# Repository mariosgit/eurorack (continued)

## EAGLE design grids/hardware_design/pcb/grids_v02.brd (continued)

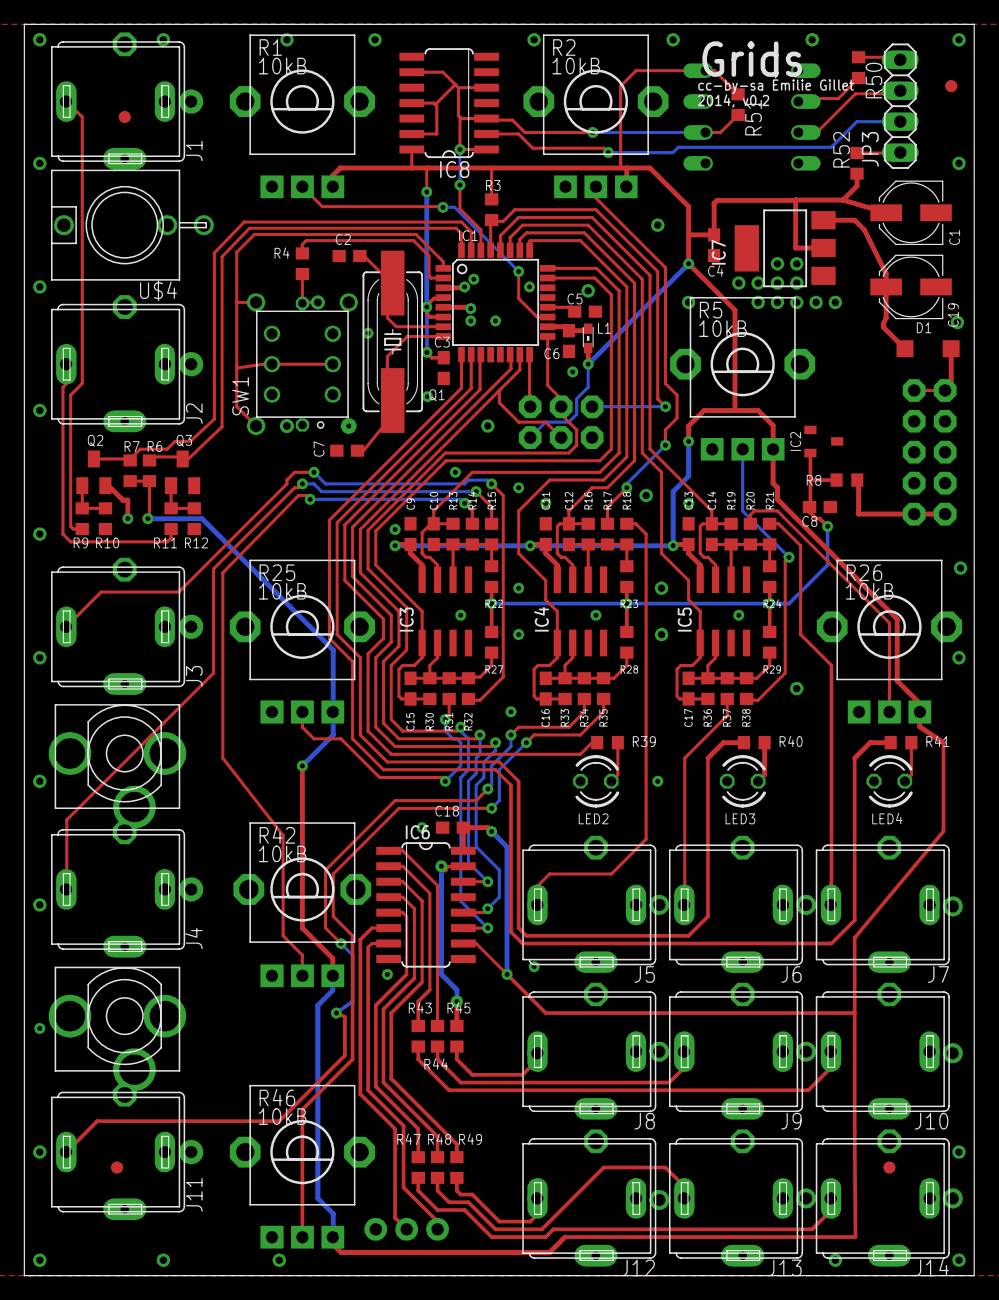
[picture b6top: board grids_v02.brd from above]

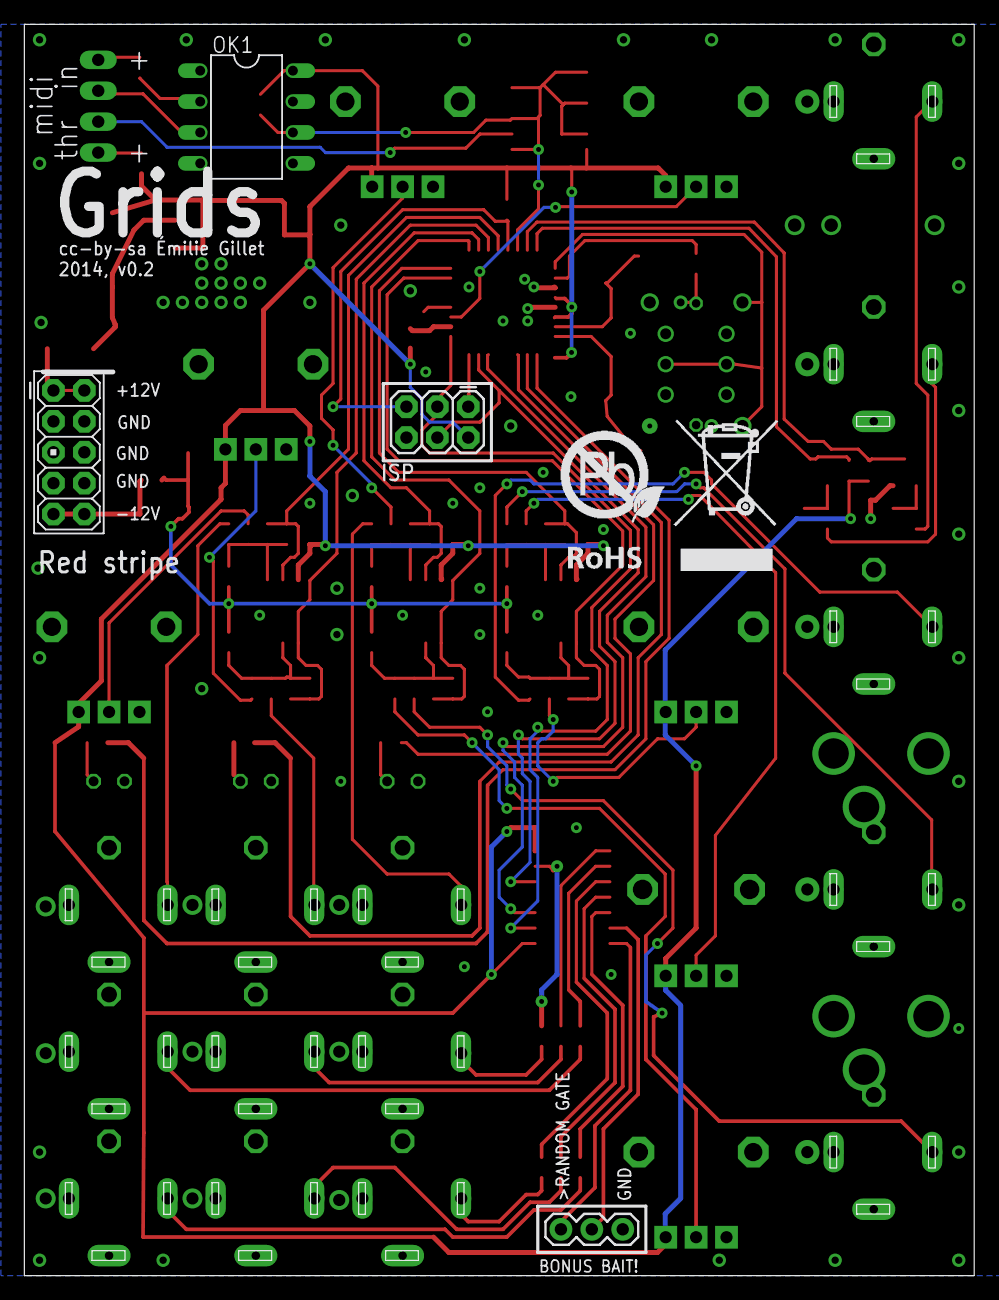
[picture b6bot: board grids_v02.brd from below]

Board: 2 copper layers, 78.1 x 102.9 mm, 115 parts (5 on the bottom side), 75 nets.

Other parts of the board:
U$2: ROHS_BIG

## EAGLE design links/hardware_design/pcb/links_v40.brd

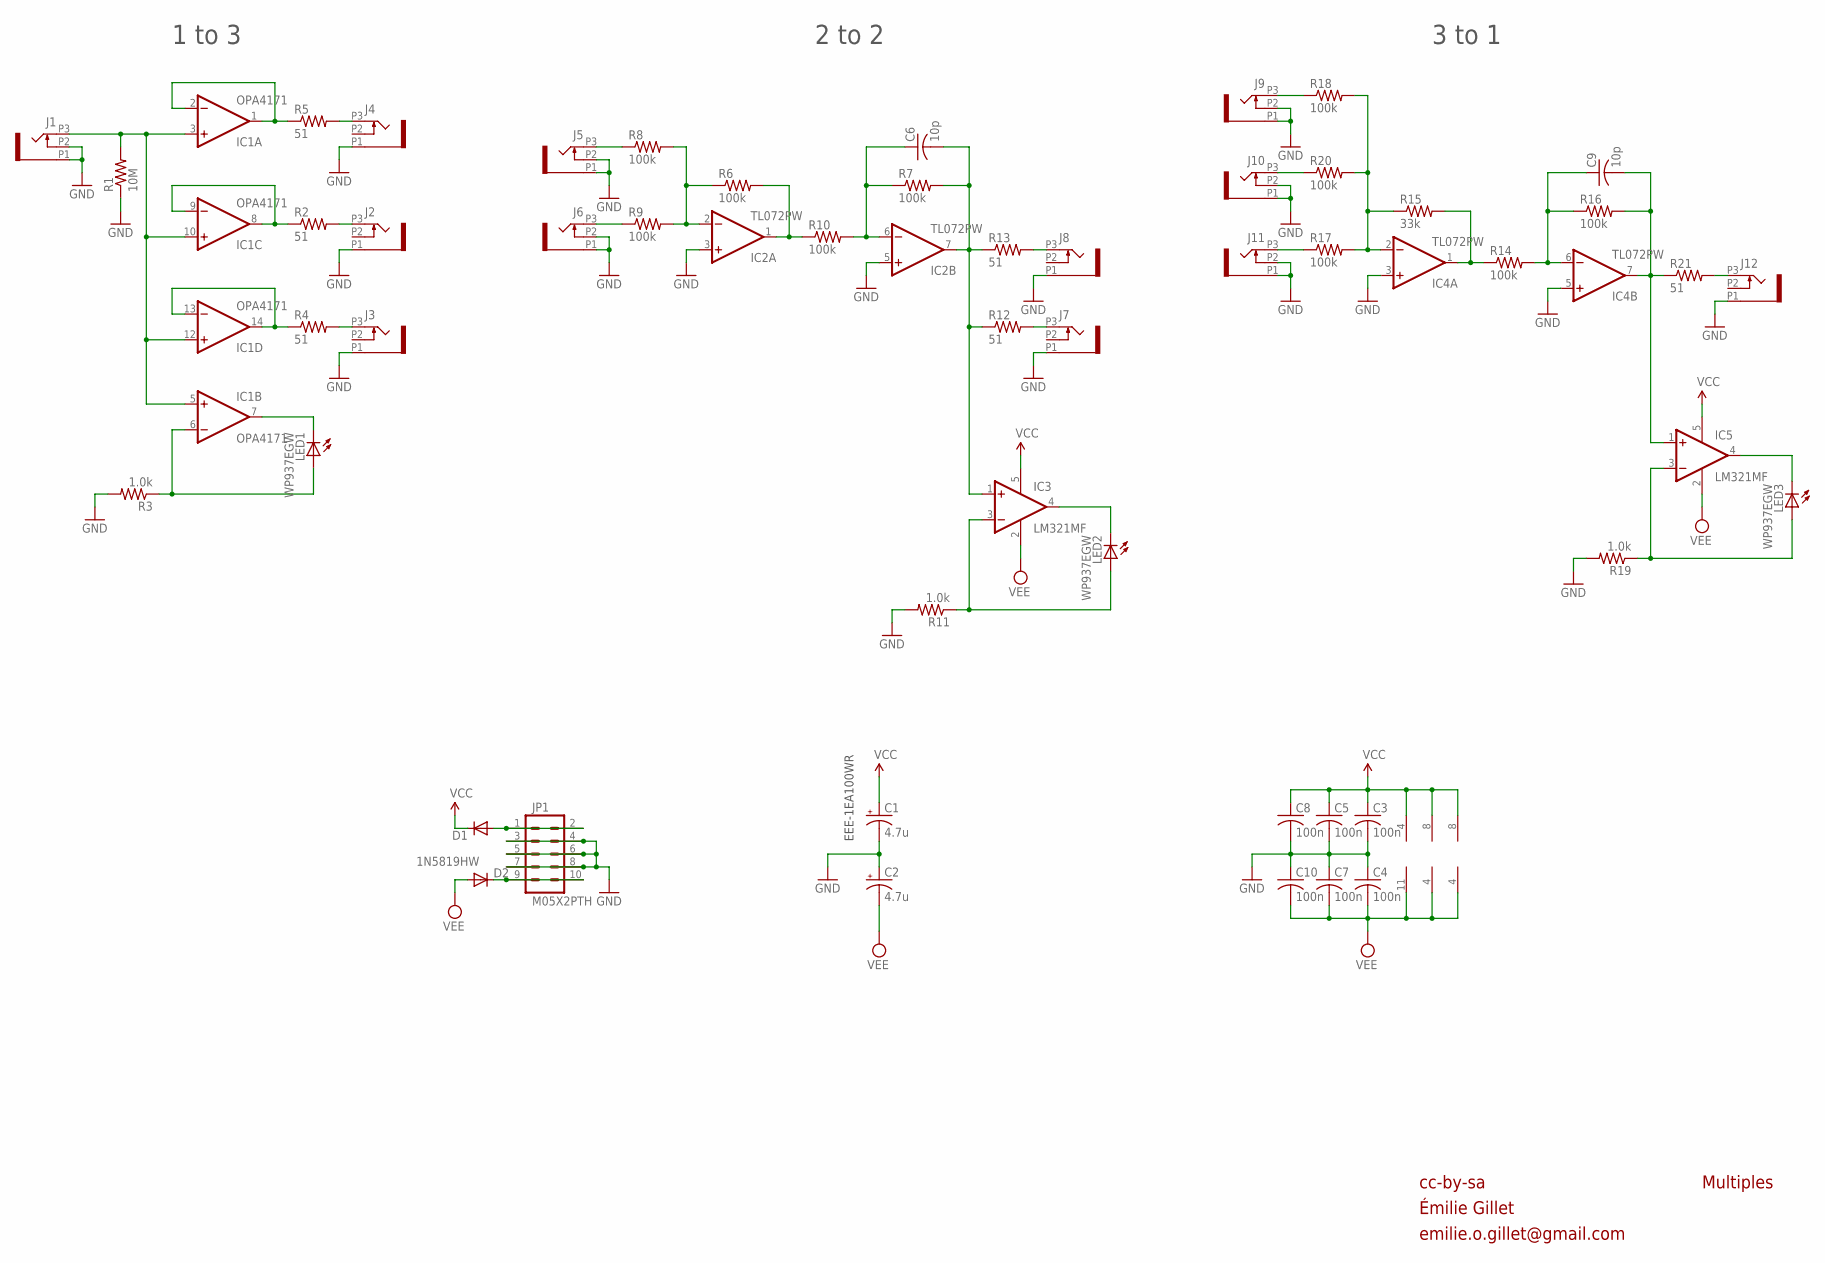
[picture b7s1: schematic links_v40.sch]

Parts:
C1, C2: 4.7u; PANASONIC_A
C3, C4, C5, C7, C8, C10: 100n; C0603
C6, C9: 10p; C0603
D1, D2: 1N5819HW; SOD123
IC1: OPA4171; TSSOP14
IC2, IC4: TL072PW; TSSOP8
IC3, IC5: LM321MF; SOT23-5
J1, J2, J3, J4, J5, J6, J7, J8, J9, J10, J11, J12: PJ301_THONKICONN6; WQP_PJ_301M6
JP1: M05X2PTH; AVR_ICSP
LED1, LED2, LED3: WP937EGW; LED3MM
R1: 10M; R0603
R2, R4, R5, R12, R13, R21: 51; R0603
R3, R11, R19: 1.0k; R0603
R6, R7, R8, R9, R10, R14, R16, R17, R18, R20: 100k; R0603
R15: 33k; R0603

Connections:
GND: C1.-, C2.+, C3.2, C4.1, C5.2, C7.1, C8.2, C10.1, IC2.3 (+IN), IC2.5 (+IN), IC4.3 (+IN), IC4.5 (+IN), J1.P1 (1), J1.P2 (2), J2.P1 (1), J3.P1 (1), J4.P1 (1), J5.P1 (1), J5.P2 (2), J6.P1 (1), J6.P2 (2), J7.P1 (1), J8.P1 (1), J9.P1 (1), J9.P2 (2), J10.P1 (1), J10.P2 (2), J11.P1 (1), J11.P2 (2), J12.P1 (1), JP1.3, JP1.4, JP1.5, JP1.6, JP1.7, JP1.8, R1.1, R3.2, R11.2, R19.2
unnamed: IC2.1 (OUT), R6.2, R10.1
unnamed: J11.P3 (3), R17.1
unnamed: IC1.1 (OUT), IC1.2 (-IN), R5.1
unnamed: IC1.8 (OUT), IC1.9 (-IN), R2.1
unnamed: IC1.13 (-IN), IC1.14 (OUT), R4.1
unnamed: D1.A, JP1.1, JP1.2
unnamed: IC1.3 (+IN), IC1.5 (+IN), IC1.10 (+IN), IC1.12 (+IN), J1.P3 (3), R1.2
unnamed: IC1.7 (OUT), LED1.K (C)
unnamed: J10.P3 (3), R20.1
unnamed: J6.P3 (3), R9.1
unnamed: J4.P3 (3), R5.2
unnamed: J2.P3 (3), R2.2
unnamed: J3.P3 (3), R4.2
unnamed: IC3.4 (OUT), LED2.K (C)
unnamed: J5.P3 (3), R8.1
unnamed: J7.P3 (3), R12.2
unnamed: J8.P3 (3), R13.2
unnamed: C9.2, IC4.7 (OUT), IC5.1 (+IN), R16.2, R21.1
unnamed: IC5.3 (-IN), LED3.A, R19.1
unnamed: D2.C, JP1.9, JP1.10
unnamed: IC1.6 (-IN), LED1.A, R3.1
unnamed: J9.P3 (3), R18.1
unnamed: J12.P3 (3), R21.2
unnamed: IC4.2 (-IN), R15.1, R17.2, R18.2, R20.2
unnamed: IC4.1 (OUT), R14.1, R15.2
unnamed: C6.2, IC2.7 (OUT), IC3.1 (+IN), R7.2, R12.1, R13.1
unnamed: C9.1, IC4.6 (-IN), R14.2, R16.1
unnamed: IC3.3 (-IN), LED2.A, R11.1
unnamed: IC5.4 (OUT), LED3.K (C)
unnamed: IC2.2 (-IN), R6.1, R8.2, R9.2
unnamed: C6.1, IC2.6 (-IN), R7.1, R10.2
VCC: C1.+, C3.1, C5.1, C8.1, D1.C, IC1.4 (V+), IC2.8 (V+), IC3.5 (V+), IC4.8 (V+), IC5.5 (V+)
VEE: C2.-, C4.2, C7.2, C10.2, D2.A, IC1.11 (V-), IC2.4 (V-), IC3.2 (V-), IC4.4 (V-), IC5.2 (V-)

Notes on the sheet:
cc-by-sa
Multiples
1 to 3
2 to 2
3 to 1
EEE-1EA100WR
Émilie Gillet
emilie.o.gillet@gmail.com

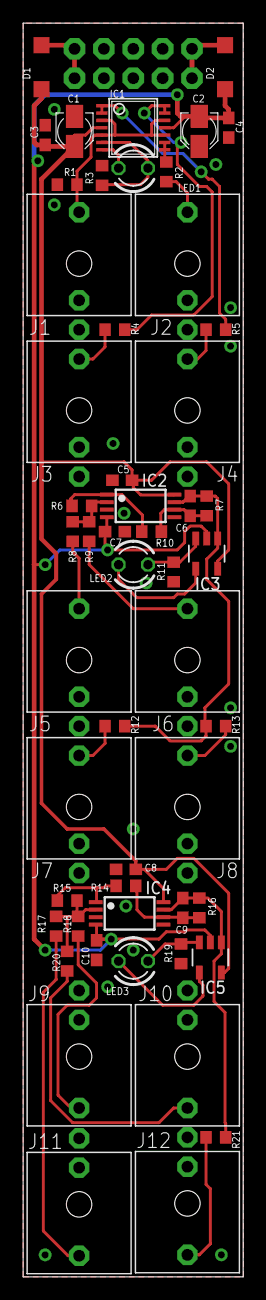
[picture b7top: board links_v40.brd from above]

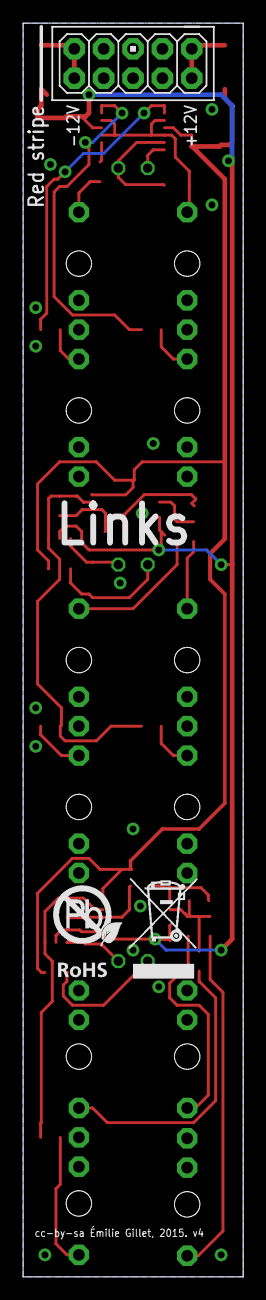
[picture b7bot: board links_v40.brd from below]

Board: 2 copper layers, 19.0 x 108.4 mm, 55 parts (2 on the bottom side), 34 nets.

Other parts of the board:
U$2: ROHS

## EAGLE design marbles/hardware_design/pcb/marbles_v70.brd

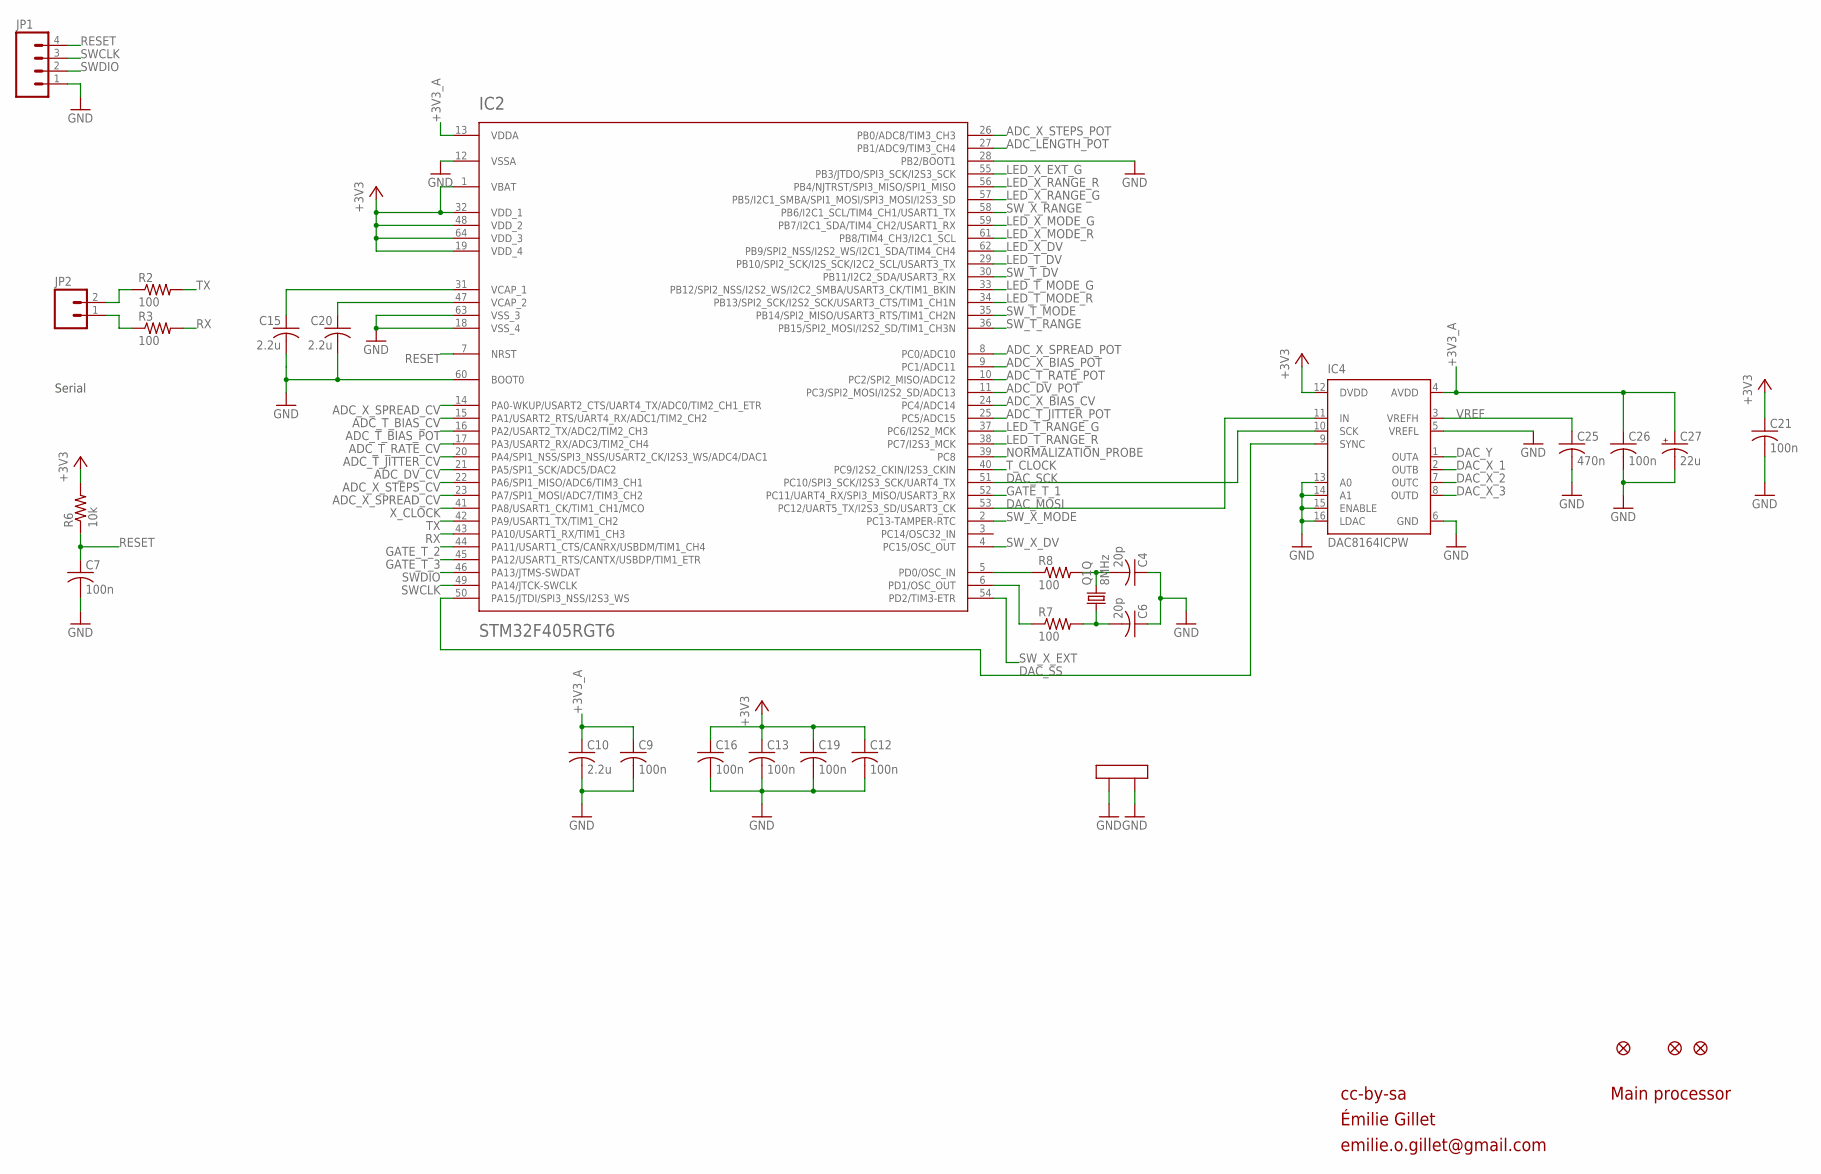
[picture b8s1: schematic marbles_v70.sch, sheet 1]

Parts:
C4, C6: 20p; C0603
C7, C9, C12, C13, C16, C19, C21, C26: 100n; C0603
C10, C15, C20: 2.2u; C0805
C25: 470n; C0603
C27: 22u; PANASONIC_C
F1, F2, F3: FIDUCIAL1X2; FIDUCIAL-1X2
IC2: STM32F405RGT6; TQFP-10X10-64
IC4: DAC8164ICPW; SOP65P640X110-16N
JP1: M04PTH; 1X04
JP2: M02PTH; 1X02
Q1: 8MHz; CTS406
R2, R3, R7, R8: 100; R0603
R6: 10k; R0603

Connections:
+3V3: C12.1, C13.1, C16.1, C19.1, C21.1, IC2.1 (VBAT), IC2.19 (VDD_4), IC2.32 (VDD_1), IC2.48 (VDD_2), IC2.64 (VDD_3), IC4.12 (DVDD), R6.2; also elsewhere on the board
+3V3_A: C9.1, C10.1, C26.1, C27.+, IC2.13 (VDDA), IC4.4 (AVDD); also elsewhere on the board
ADC_DV_CV: IC2.21 (PA5/SPI1_SCK/ADC5/DAC2); also elsewhere on the board
ADC_DV_POT: IC2.11 (PC3/SPI2_MOSI/I2S2_SD/ADC13); also elsewhere on the board
ADC_LENGTH_POT: IC2.27 (PB1/ADC9/TIM3_CH4); also elsewhere on the board
ADC_T_BIAS_CV: IC2.15 (PA1/USART2_RTS/UART4_RX/ADC1/TIM2_CH2); also elsewhere on the board
ADC_T_BIAS_POT: IC2.16 (PA2/USART2_TX/ADC2/TIM2_CH3); also elsewhere on the board
ADC_T_JITTER_CV: IC2.20 (PA4/SPI1_NSS/SPI3_NSS/USART2_CK/I2S3_WS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); also elsewhere on the board
ADC_T_JITTER_POT: IC2.25 (PC5/ADC15); also elsewhere on the board
ADC_T_RATE_CV: IC2.17 (PA3/USART2_RX/ADC3/TIM2_CH4); also elsewhere on the board
ADC_T_RATE_POT: IC2.10 (PC2/SPI2_MISO/ADC12); also elsewhere on the board
ADC_X_BIAS_CV: IC2.24 (PC4/ADC14); also elsewhere on the board
ADC_X_BIAS_POT: IC2.9 (PC1/ADC11); also elsewhere on the board
ADC_X_SPREAD_CV: IC2.14 (PA0-WKUP/USART2_CTS/UART4_TX/ADC0/TIM2_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), IC2.23 (PA7/SPI1_MOSI/ADC7/TIM3_CH2); also elsewhere on the board
ADC_X_SPREAD_POT: IC2.8 (PC0/ADC10); also elsewhere on the board
ADC_X_STEPS_CV: IC2.22 (PA6/SPI1_MISO/ADC6/TIM3_CH1); also elsewhere on the board
ADC_X_STEPS_POT: IC2.26 (PB0/ADC8/TIM3_CH3); also elsewhere on the board
DAC_MOSI: IC2.53 (PC12/UART5_TX/I2S3_SD/USART3_CK), IC4.11 (IN)
DAC_SCK: IC2.51 (PC10/SPI3_SCK/I2S3_SCK/UART4_TX), IC4.10 (SCK)
DAC_SS: IC2.50 (PA15/JTDI/SPI3_NSS/I2S3_WS), IC4.9 (SYNC)
DAC_X_1: IC4.2 (OUTB); also elsewhere on the board
DAC_X_2: IC4.7 (OUTC); also elsewhere on the board
DAC_X_3: IC4.8 (OUTD); also elsewhere on the board
DAC_Y: IC4.1 (OUTA); also elsewhere on the board
GATE_T_1: IC2.52 (PC11/UART4_RX/SPI3_MISO/USART3_RX); also elsewhere on the board
GATE_T_2: IC2.44 (PA11/USART1_CTS/CANRX/USBDM/TIM1_CH4); also elsewhere on the board
GATE_T_3: IC2.45 (PA12/USART1_RTS/CANTX/USBDP/TIM1_ETR); also elsewhere on the board
GND: C4.1, C6.1, C7.2, C9.2, C10.2, C12.2, C13.2, C15.2, C16.2, C19.2, C20.2, C21.2, C25.2, C26.2, C27.-, IC2.12 (VSSA), IC2.18 (VSS_4), IC2.28 (PB2/BOOT1), IC2.60 (BOOT0), IC2.63 (VSS_3), IC4.5 (VREFL), IC4.6 (GND), IC4.13 (A0), IC4.14 (A1), IC4.15 (ENABLE), IC4.16 (LDAC), JP1.1, Q1.2 (LID1), Q1.4 (LID2); also elsewhere on the board
LED_T_DV: IC2.29 (PB10/SPI2_SCK/I2S_SCK/I2C2_SCL/USART3_TX); also elsewhere on the board
LED_T_MODE_G: IC2.33 (PB12/SPI2_NSS/I2S2_WS/I2C2_SMBA/USART3_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); also elsewhere on the board
LED_T_MODE_R: IC2.34 (PB13/SPI2_SCK/I2S2_SCK/USART3_CTS/TIM1_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); also elsewhere on the board
LED_T_RANGE_G: IC2.37 (PC6/I2S2_MCK); also elsewhere on the board
LED_T_RANGE_R: IC2.38 (PC7/I2S3_MCK); also elsewhere on the board
LED_X_DV: IC2.62 (PB9/SPI2_NSS/I2S2_WS/I2C1_SDA/TIM4_CH4); also elsewhere on the board
LED_X_EXT_G: IC2.55 (PB3/JTDO/SPI3_SCK/I2S3_SCK); also elsewhere on the board
LED_X_MODE_G: IC2.59 (PB7/I2C1_SDA/TIM4_CH2/USART1_RX); also elsewhere on the board
LED_X_MODE_R: IC2.61 (PB8/TIM4_CH3/I2C1_SCL); also elsewhere on the board
LED_X_RANGE_G: IC2.57 (PB5/I2C1_SMBA/SPI1_MOSI/SPI3_MOSI/I2S3_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); also elsewhere on the board
LED_X_RANGE_R: IC2.56 (PB4/NJTRST/SPI3_MISO/SPI1_MISO); also elsewhere on the board
unnamed: IC2.6 (PD1/OSC_OUT), R7.1
unnamed: IC2.5 (PD0/OSC_IN), R8.1
unnamed: C20.1, IC2.47 (VCAP_2)
unnamed: C15.1, IC2.31 (VCAP_1)
unnamed: JP2.2, R2.1
unnamed: JP2.1, R3.1
unnamed: C4.2, Q1.3 (2), R8.2
unnamed: C6.2, Q1.1, R7.2
NORMALIZATION_PROBE: IC2.39 (PC8); also elsewhere on the board
RESET: C7.1, IC2.7 (NRST), JP1.4, R6.1
RX: IC2.43 (PA10/USART1_RX/TIM1_CH3), R3.2
SWCLK: IC2.49 (PA14/JTCK-SWCLK), JP1.3
SWDIO: IC2.46 (PA13/JTMS-SWDAT), JP1.2
SW_T_DV: IC2.30 (PB11/I2C2_SDA/USART3_RX); also elsewhere on the board
SW_T_MODE: IC2.35 (PB14/SPI2_MISO/USART3_RTS/TIM1_CH2N); also elsewhere on the board
SW_T_RANGE: IC2.36 (PB15/SPI2_MOSI/I2S2_SD/TIM1_CH3N); also elsewhere on the board
SW_X_DV: IC2.4 (PC15/OSC_OUT); also elsewhere on the board
SW_X_EXT: IC2.54 (PD2/TIM3-ETR); also elsewhere on the board
SW_X_MODE: IC2.2 (PC13-TAMPER-RTC); also elsewhere on the board
SW_X_RANGE: IC2.58 (PB6/I2C1_SCL/TIM4_CH1/USART1_TX); also elsewhere on the board
TX: IC2.42 (PA9/USART1_TX/TIM1_CH2), R2.2
T_CLOCK: IC2.40 (PC9/I2S2_CKIN/I2S3_CKIN); also elsewhere on the board
VREF: C25.1, IC4.3 (VREFH); also elsewhere on the board
X_CLOCK: IC2.41 (PA8/USART1_CK/TIM1_CH1/MCO); also elsewhere on the board

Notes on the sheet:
cc-by-sa
Main processor
Serial
Émilie Gillet
emilie.o.gillet@gmail.com

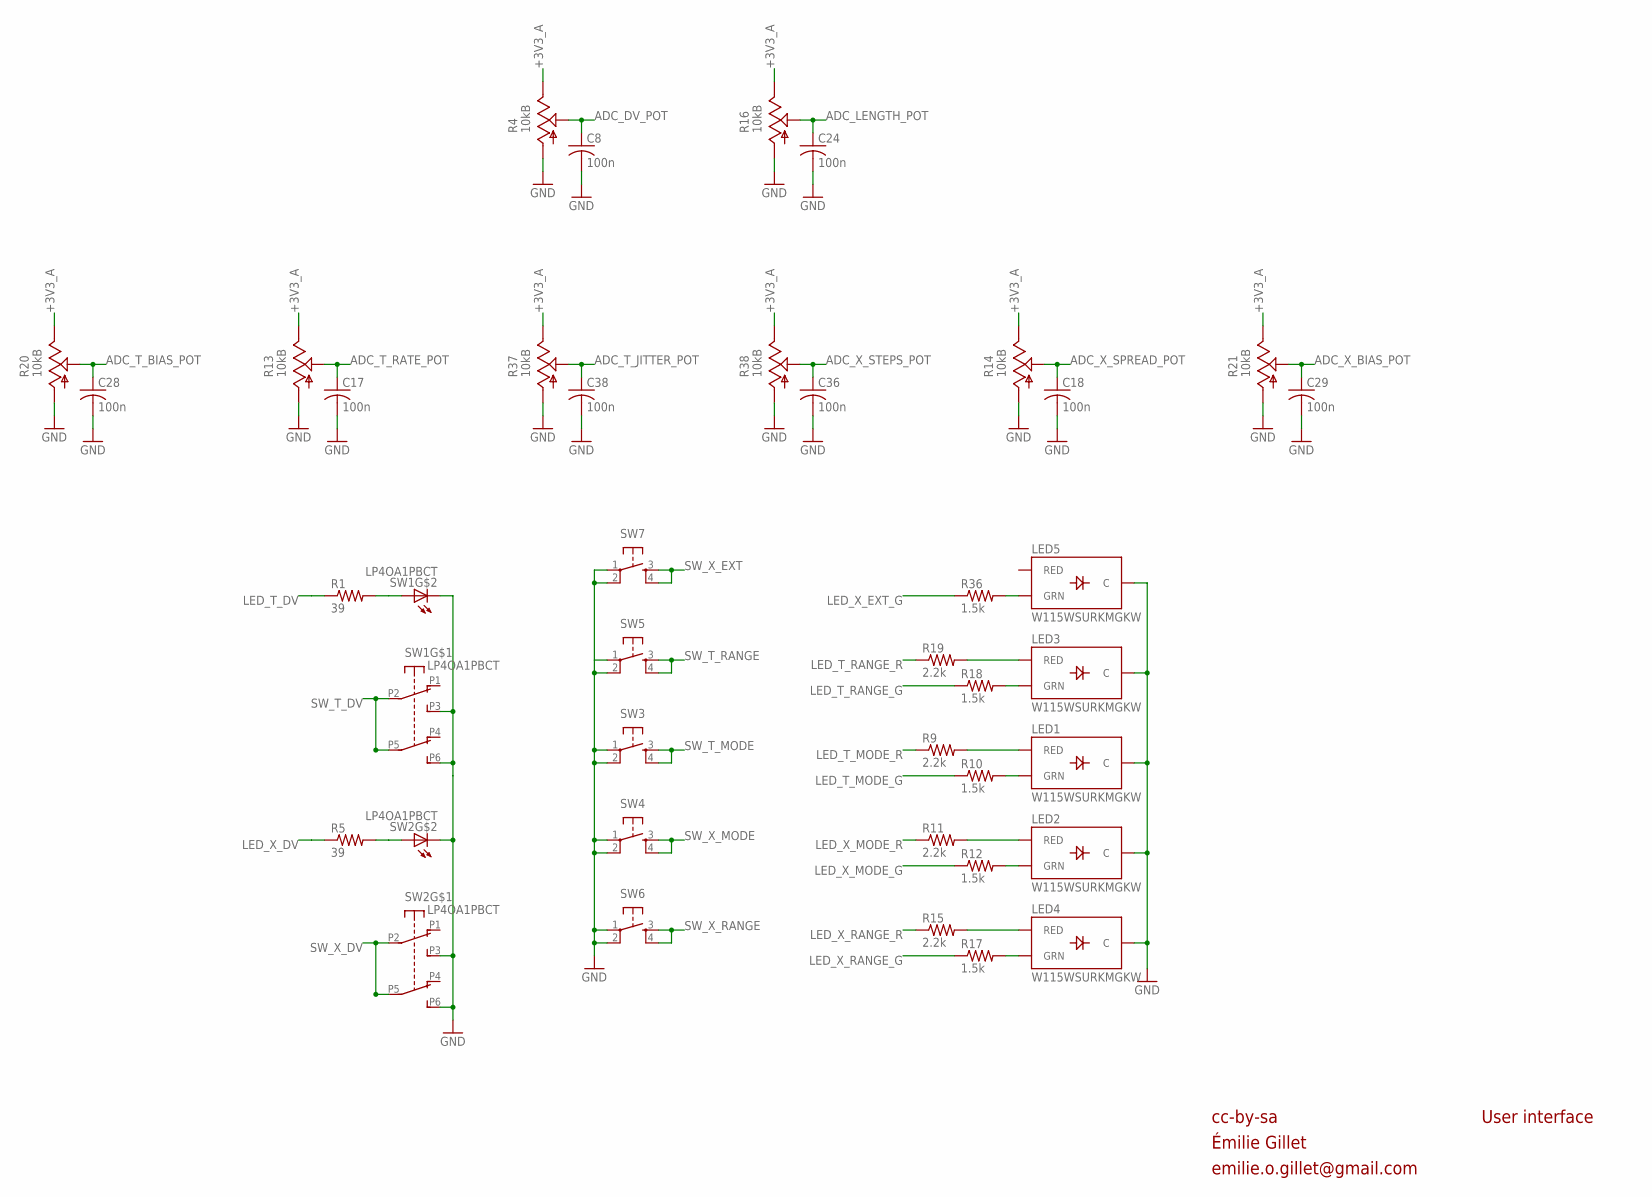
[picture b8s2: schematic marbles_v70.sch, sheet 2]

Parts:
C8, C17, C18, C24, C28, C29, C36, C38: 100n; C0603
LED1, LED2, LED3, LED4, LED5: W115WSURKMGKW; LED-BICOLOR-THROUGHHOLE-2.54
R1, R5: 39; R0603
R4, R13, R14, R16, R20, R21, R37, R38: 10kB; ALPS_POT_VERTICAL_PS
R9, R11, R15, R19: 2.2k; R0603
R10, R12, R17, R18, R36: 1.5k; R0603
SW1, SW2: LP4OA1PBCT
SW3, SW4, SW5, SW6, SW7: TAC_SWITCHPTH; TACTILE-PTH

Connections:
+3V3_A: R4.P$1 (E), R13.P$1 (E), R14.P$1 (E), R16.P$1 (E), R20.P$1 (E), R21.P$1 (E), R37.P$1 (E), R38.P$1 (E); also elsewhere on the board
ADC_DV_POT: C8.1, R4.P$2 (S); also elsewhere on the board
ADC_LENGTH_POT: C24.1, R16.P$2 (S); also elsewhere on the board
ADC_T_BIAS_POT: C28.1, R20.P$2 (S); also elsewhere on the board
ADC_T_JITTER_POT: C38.1, R37.P$2 (S); also elsewhere on the board
ADC_T_RATE_POT: C17.1, R13.P$2 (S); also elsewhere on the board
ADC_X_BIAS_POT: C29.1, R21.P$2 (S); also elsewhere on the board
ADC_X_SPREAD_POT: C18.1, R14.P$2 (S); also elsewhere on the board
ADC_X_STEPS_POT: C36.1, R38.P$2 (S); also elsewhere on the board
GND: C8.2, C17.2, C18.2, C24.2, C28.2, C29.2, C36.2, C38.2, LED1.2 (C), LED2.2 (C), LED3.2 (C), LED4.2 (C), LED5.2 (C), R4.P$3 (A), R13.P$3 (A), R14.P$3 (A), R16.P$3 (A), R20.P$3 (A), R21.P$3 (A), R37.P$3 (A), R38.P$3 (A), SW1.L2, SW1.P3 (A3), SW1.P6 (B3), SW2.L2, SW2.P3 (A3), SW2.P6 (B3), SW3.1, SW3.2, SW4.1, SW4.2, SW5.1, SW5.2, SW6.1, SW6.2, SW7.1, SW7.2; also elsewhere on the board
LED_T_DV: R1.1; also elsewhere on the board
LED_T_MODE_G: R10.1; also elsewhere on the board
LED_T_MODE_R: R9.1; also elsewhere on the board
LED_T_RANGE_G: R18.1; also elsewhere on the board
LED_T_RANGE_R: R19.1; also elsewhere on the board
LED_X_DV: R5.1; also elsewhere on the board
LED_X_EXT_G: R36.1; also elsewhere on the board
LED_X_MODE_G: R12.1; also elsewhere on the board
LED_X_MODE_R: R11.1; also elsewhere on the board
LED_X_RANGE_G: R17.1; also elsewhere on the board
LED_X_RANGE_R: R15.1; also elsewhere on the board
unnamed: R1.2, SW1.L1
unnamed: R5.2, SW2.L1
unnamed: LED3.3 (RED), R19.2
unnamed: LED3.1 (GRN), R18.2
unnamed: LED1.3 (RED), R9.2
unnamed: LED2.3 (RED), R11.2
unnamed: LED2.1 (GRN), R12.2
unnamed: LED4.3 (RED), R15.2
unnamed: LED1.1 (GRN), R10.2
unnamed: LED4.1 (GRN), R17.2
unnamed: LED5.1 (GRN), R36.2
SW_T_DV: SW1.P2 (A2), SW1.P5 (B2); also elsewhere on the board
SW_T_MODE: SW3.3, SW3.4; also elsewhere on the board
SW_T_RANGE: SW5.3, SW5.4; also elsewhere on the board
SW_X_DV: SW2.P2 (A2), SW2.P5 (B2); also elsewhere on the board
SW_X_EXT: SW7.3, SW7.4; also elsewhere on the board
SW_X_MODE: SW4.3, SW4.4; also elsewhere on the board
SW_X_RANGE: SW6.3, SW6.4; also elsewhere on the board

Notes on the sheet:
cc-by-sa
User interface
Émilie Gillet
emilie.o.gillet@gmail.com

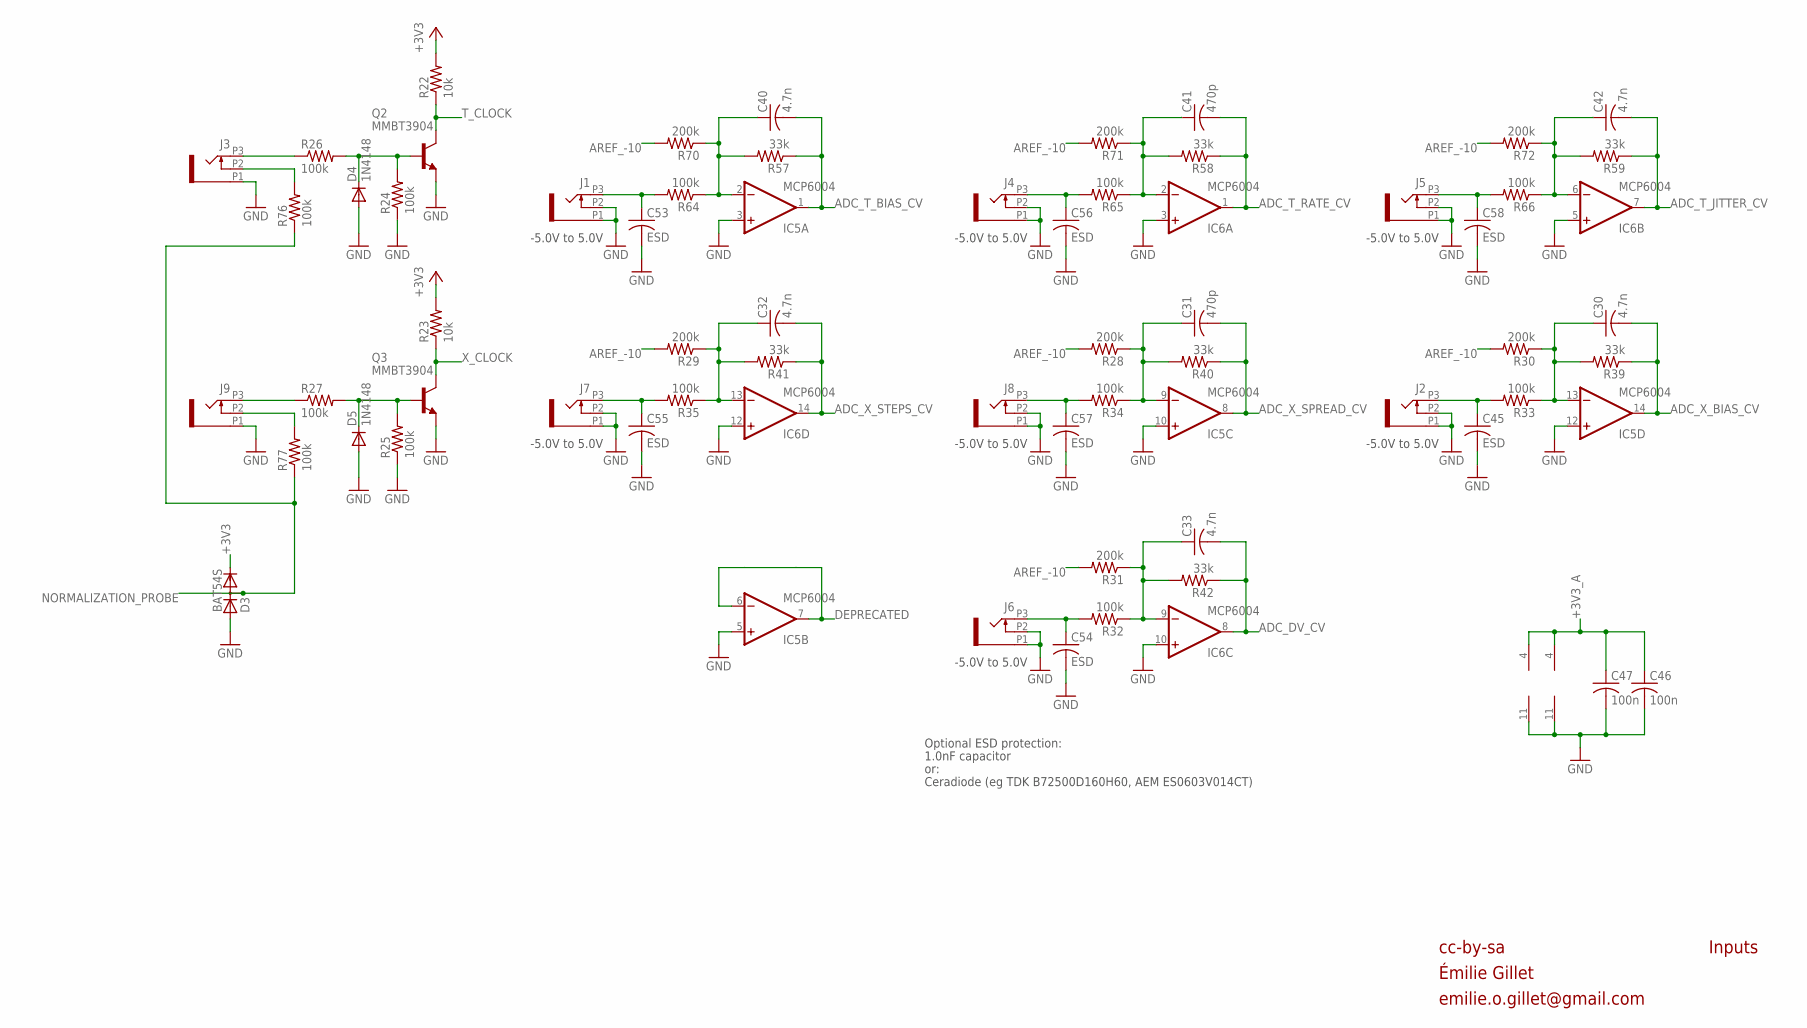
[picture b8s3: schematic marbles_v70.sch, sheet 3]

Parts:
C30, C32, C33, C40, C42: 4.7n; C0603
C31, C41: 470p; C0603
C45, C53, C54, C55, C56, C57, C58: ESD; C0603
C46, C47: 100n; C0603
D3: BAT54S; SOT23
D4, D5: 1N4148; SOD523
IC5, IC6: MCP6004; TSSOP14_065
J1, J2, J3, J4, J5, J6, J7, J8, J9: PJ301_THONKICONN6; WQP_PJ_301M6
Q2, Q3: MMBT3904; SOT23-BEC
R22, R23: 10k; R0603
R24, R25, R26, R27, R32, R33, R34, R35, R64, R65, R66, R76, R77: 100k; R0603
R28, R29, R30, R31, R70, R71, R72: 200k; R0603
R39, R40, R41, R42, R57, R58, R59: 33k; R0603

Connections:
+3V3: D3.2 (C), R22.2, R23.2; also elsewhere on the board
+3V3_A: C46.1, C47.1, IC5.4 (V+), IC6.4 (V+); also elsewhere on the board
ADC_DV_CV: C33.2, IC6.8 (OUT), R42.1; also elsewhere on the board
ADC_T_BIAS_CV: C40.2, IC5.1 (OUT), R57.1; also elsewhere on the board
ADC_T_JITTER_CV: C42.2, IC6.7 (OUT), R59.1; also elsewhere on the board
ADC_T_RATE_CV: C41.2, IC6.1 (OUT), R58.1; also elsewhere on the board
ADC_X_BIAS_CV: C30.2, IC5.14 (OUT), R39.1; also elsewhere on the board
ADC_X_SPREAD_CV: C31.2, IC5.8 (OUT), R40.1; also elsewhere on the board
ADC_X_STEPS_CV: C32.2, IC6.14 (OUT), R41.1; also elsewhere on the board
AREF_-10: R28.2, R29.2, R30.2, R31.2, R70.2, R71.2, R72.2; also elsewhere on the board
DEPRECATED: IC5.6 (-IN), IC5.7 (OUT)
GND: C45.2, C46.2, C47.2, C53.2, C54.2, C55.2, C56.2, C57.2, C58.2, D3.1 (A), D4.A, D5.A, IC5.3 (+IN), IC5.5 (+IN), IC5.10 (+IN), IC5.11 (V-), IC5.12 (+IN), IC6.3 (+IN), IC6.5 (+IN), IC6.10 (+IN), IC6.11 (V-), IC6.12 (+IN), J1.P1 (1), J1.P2 (2), J2.P1 (1), J2.P2 (2), J3.P1 (1), J4.P1 (1), J4.P2 (2), J5.P1 (1), J5.P2 (2), J6.P1 (1), J6.P2 (2), J7.P1 (1), J7.P2 (2), J8.P1 (1), J8.P2 (2), J9.P1 (1), Q2.E, Q3.E, R24.1, R25.1; also elsewhere on the board
MORPH_IN: C53.1, J1.P3 (3), R64.2
MORPH_IN1: C55.1, J7.P3 (3), R35.2
MORPH_IN3: C56.1, J4.P3 (3), R65.2
MORPH_IN4: C57.1, J8.P3 (3), R34.2
MORPH_IN5: C54.1, J6.P3 (3), R32.2
MORPH_IN6: C58.1, J5.P3 (3), R66.2
MORPH_IN7: C45.1, J2.P3 (3), R33.2
unnamed: C41.1, IC6.2 (-IN), R58.2, R65.1, R71.1
unnamed: C40.1, IC5.2 (-IN), R57.2, R64.1, R70.1
unnamed: C42.1, IC6.6 (-IN), R59.2, R66.1, R72.1
unnamed: C31.1, IC5.9 (-IN), R28.1, R34.1, R40.2
unnamed: C30.1, IC5.13 (-IN), R30.1, R33.1, R39.2
unnamed: C32.1, IC6.13 (-IN), R29.1, R35.1, R41.2
unnamed: C33.1, IC6.9 (-IN), R31.1, R32.1, R42.2
unnamed: J9.P3 (3), R27.1
unnamed: J9.P2 (2), R77.2
unnamed: J3.P2 (2), R76.2
unnamed: D4.C, Q2.B, R24.2, R26.2
unnamed: D5.C, Q3.B, R25.2, R27.2
unnamed: J3.P3 (3), R26.1
NORMALIZATION_PROBE: D3.3 (AC), R76.1, R77.1; also elsewhere on the board
T_CLOCK: Q2.C, R22.1; also elsewhere on the board
X_CLOCK: Q3.C, R23.1; also elsewhere on the board

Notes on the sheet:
cc-by-sa
Inputs
-5.0V to 5.0V
Optional ESD protection:
1.0nF capacitor
or:
Ceradiode (eg TDK B72500D160H60, AEM ES0603V014CT)
Émilie Gillet
emilie.o.gillet@gmail.com
